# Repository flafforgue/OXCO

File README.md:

# OXCO
Kicad project for 10MHz OXCO with frequency divider and multiplier
outputs 25 Mhz, 10 Mhz, 1 Mhz, 10 Khz,1 kHz ( yes 100khz is ommited but i have not enougth space on board :) 

there are 4 x 10 Mhz outputs , grouped by 2 in oposite phase
what can be done is for 2 installing filter as indicated and for the two other replacing inductance 
and output capacity by strap and not installing filter capacity for having square waves output.

composed of 2 boards
first with OXCO and precision voltage generator and buffered 10 MHz outputs
second with ICS511 multiplier ( 2.5 so 25 MHz outputs ) and 74LS390  dividers

all outputs are 50 Ohms, buffered with 3 x 74HC04 inverter and filter to keep only sine wave

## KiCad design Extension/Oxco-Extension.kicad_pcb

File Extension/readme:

extention board with dividers and multiplier module

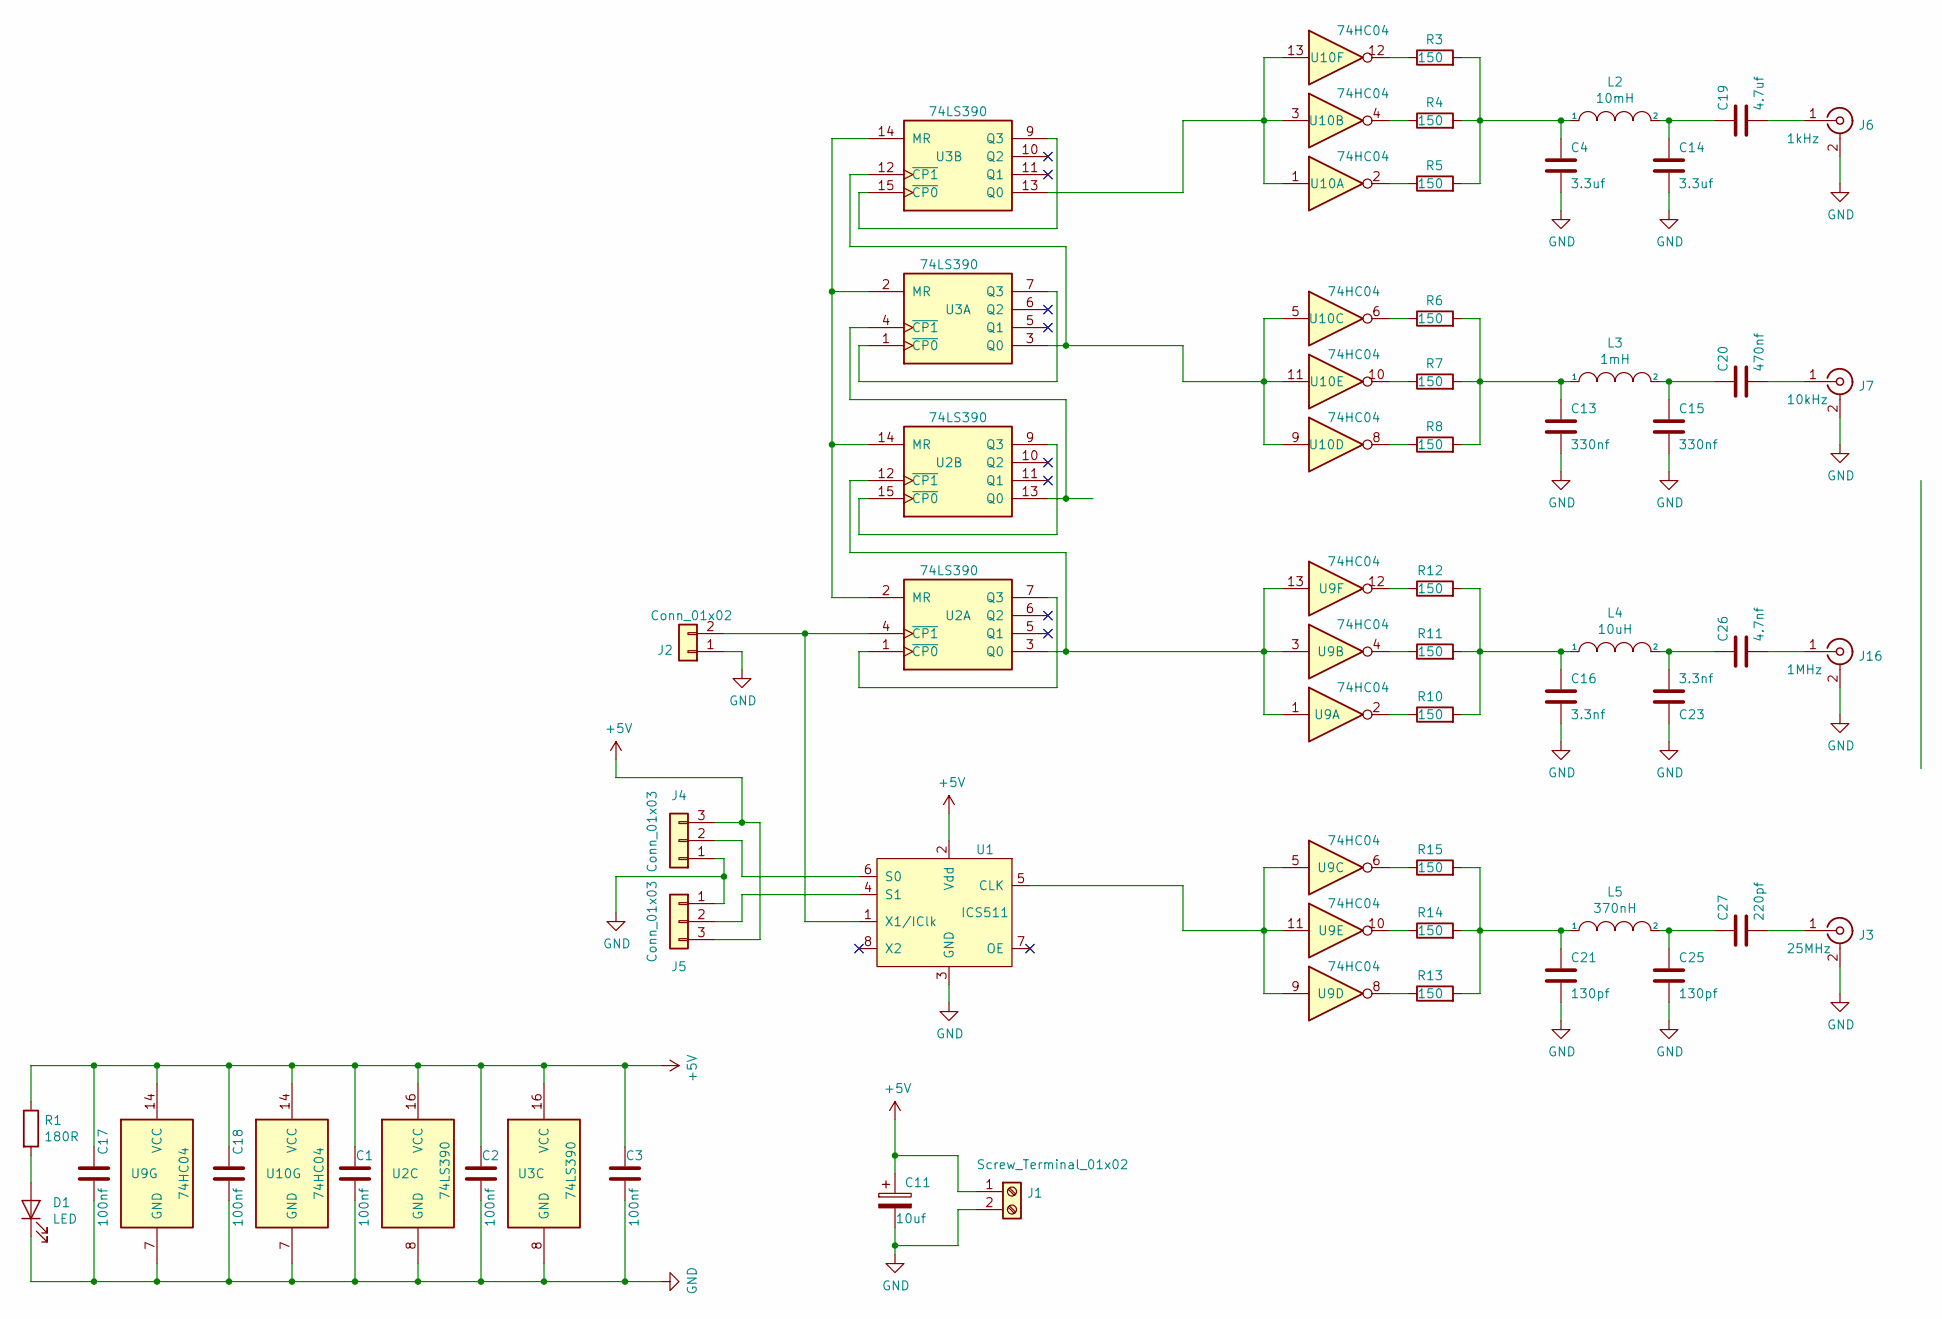
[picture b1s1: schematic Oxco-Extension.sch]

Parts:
C1, C2, C3, C17, C18: 100nf; Cx
C4, C14: 3.3uf; C_Disc_D5.0mm_W2.5mm_P5.00mm
C11: 10uf; CP_Radial_D7.5mm_P2.50mm
C13, C15: 330nf; C_Disc_D5.0mm_W2.5mm_P5.00mm
C16, C23: 3.3nf; C_Disc_D5.0mm_W2.5mm_P5.00mm
C19: 4.7uf; C_Disc_D5.0mm_W2.5mm_P5.00mm
C20: 470nf; C_Disc_D5.0mm_W2.5mm_P5.00mm
C21, C25: 130pf; C_Disc_D5.0mm_W2.5mm_P5.00mm
C26: 4.7nf; C_Disc_D5.0mm_W2.5mm_P5.00mm
C27: 220pf; C_Disc_D5.0mm_W2.5mm_P5.00mm
D1: LED; LED_D5.0mm_Clear
J1: Screw_Terminal_01x02; TerminalBlock_RND_205-00287_1x02_P5.08mm_Horizontal
J2: Conn_01x02; PinSocket_1x02_P2.54mm_Vertical
J3: 25MHz; BNC_Amphenol_B6252HB-NPP3G-50_Horizontal
J4, J5: Conn_01x03; Con_1x03_P2.54mm
J6: 1kHz; BNC_Amphenol_B6252HB-NPP3G-50_Horizontal
J7: 10kHz; BNC_Amphenol_B6252HB-NPP3G-50_Horizontal
J16: 1MHz; BNC_Amphenol_B6252HB-NPP3G-50_Horizontal
L2: 10mH; Rx
L3: 1mH; Rx
L4: 10uH; Rx
L5: 370nH; Rx
R1: 180R; H-Rx
R3, R4, R5, R6, R7, R8, R10, R11, R12, R13, R14, R15: 150; H-Rx
U1: ICS511; SOIC-8_3.9x4.9mm_P1.27mm
U2, U3: 74LS390; DIP-16_W7.62mm_Socket_LongPads
U9, U10: 74HC04; DIP-14_W7.62mm_Socket_LongPads

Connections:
+5V: C1.1, C2.1, C3.1, C11.1, C17.1, C18.1, J1.1, J4.3, J5.3, R1.1, U1.2 (Vdd), U2.16 (VCC), U3.16 (VCC), U9.14 (VCC), U10.14 (VCC)
GND: C1.2, C2.2, C3.2, C4.2, C11.2, C13.2, C14.2, C15.2, C16.2, C17.2, C18.2, C21.2, C23.1, C25.2, D1.1 (K), J1.2, J2.1, J3.2 (Ext), J4.1, J5.1, J6.2 (Ext), J7.2 (Ext), J16.2 (Ext), U1.3 (GND), U2.8 (GND), U3.8 (GND), U9.7 (GND), U10.7 (GND)
unnamed: C4.1, L2.1, R3.2, R4.2, R5.2
unnamed: C13.1, L3.1, R6.2, R7.2, R8.2
unnamed: C14.1, C19.1, L2.2
unnamed: C15.1, C20.1, L3.2
unnamed: C16.1, L4.1, R10.2, R11.2, R12.2
unnamed: C19.2, J6.1 (In)
unnamed: C20.2, J7.1 (In)
unnamed: C21.1, L5.1, R13.2, R14.2, R15.2
unnamed: C23.2, C26.1, L4.2
unnamed: C25.1, C27.1, L5.2
unnamed: C26.2, J16.1 (In)
unnamed: C27.2, J3.1 (In)
unnamed: D1.2 (A), R1.2
unnamed: J2.2, U1.1 (X1/IClk), U2.4 (~CP1)
unnamed: J4.2, U1.6 (S0)
unnamed: J5.2, U1.4 (S1)
unnamed: R3.1, U10.12
unnamed: R4.1, U10.4
unnamed: R5.1, U10.2
unnamed: R6.1, U10.6
unnamed: R7.1, U10.10
unnamed: R8.1, U10.8
unnamed: R10.1, U9.2
unnamed: R11.1, U9.4
unnamed: R12.1, U9.12
unnamed: R13.1, U9.8
unnamed: R14.1, U9.10
unnamed: R15.1, U9.6
unnamed: U1.5 (CLK), U9.5, U9.9, U9.11
unnamed: U2.1 (~CP0), U2.7 (Q3)
unnamed: U2.3 (Q0), U2.12 (~CP1), U9.1, U9.3, U9.13
unnamed: U2.13 (Q0), U3.4 (~CP1)
unnamed: U2.2 (MR), U2.14 (MR), U3.2 (MR), U3.14 (MR)
unnamed: U2.9 (Q3), U2.15 (~CP0)
unnamed: U3.1 (~CP0), U3.7 (Q3)
unnamed: U3.9 (Q3), U3.15 (~CP0)
unnamed: U3.13 (Q0), U10.1, U10.3, U10.13
unnamed: U3.3 (Q0), U3.12 (~CP1), U10.5, U10.9, U10.11

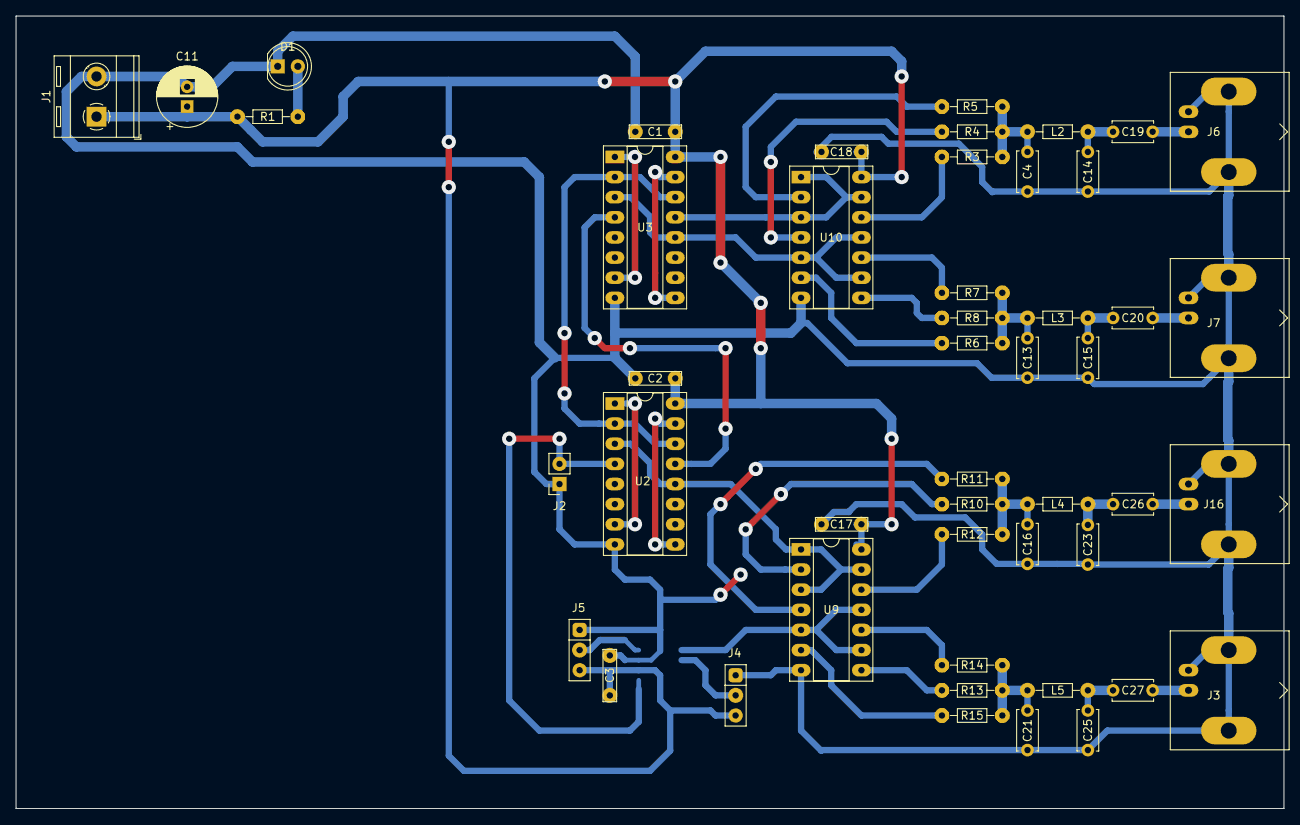
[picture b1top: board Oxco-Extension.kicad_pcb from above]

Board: 2 copper layers, 160.0 x 100.0 mm, 49 parts (1 on the bottom side), 40 nets.
